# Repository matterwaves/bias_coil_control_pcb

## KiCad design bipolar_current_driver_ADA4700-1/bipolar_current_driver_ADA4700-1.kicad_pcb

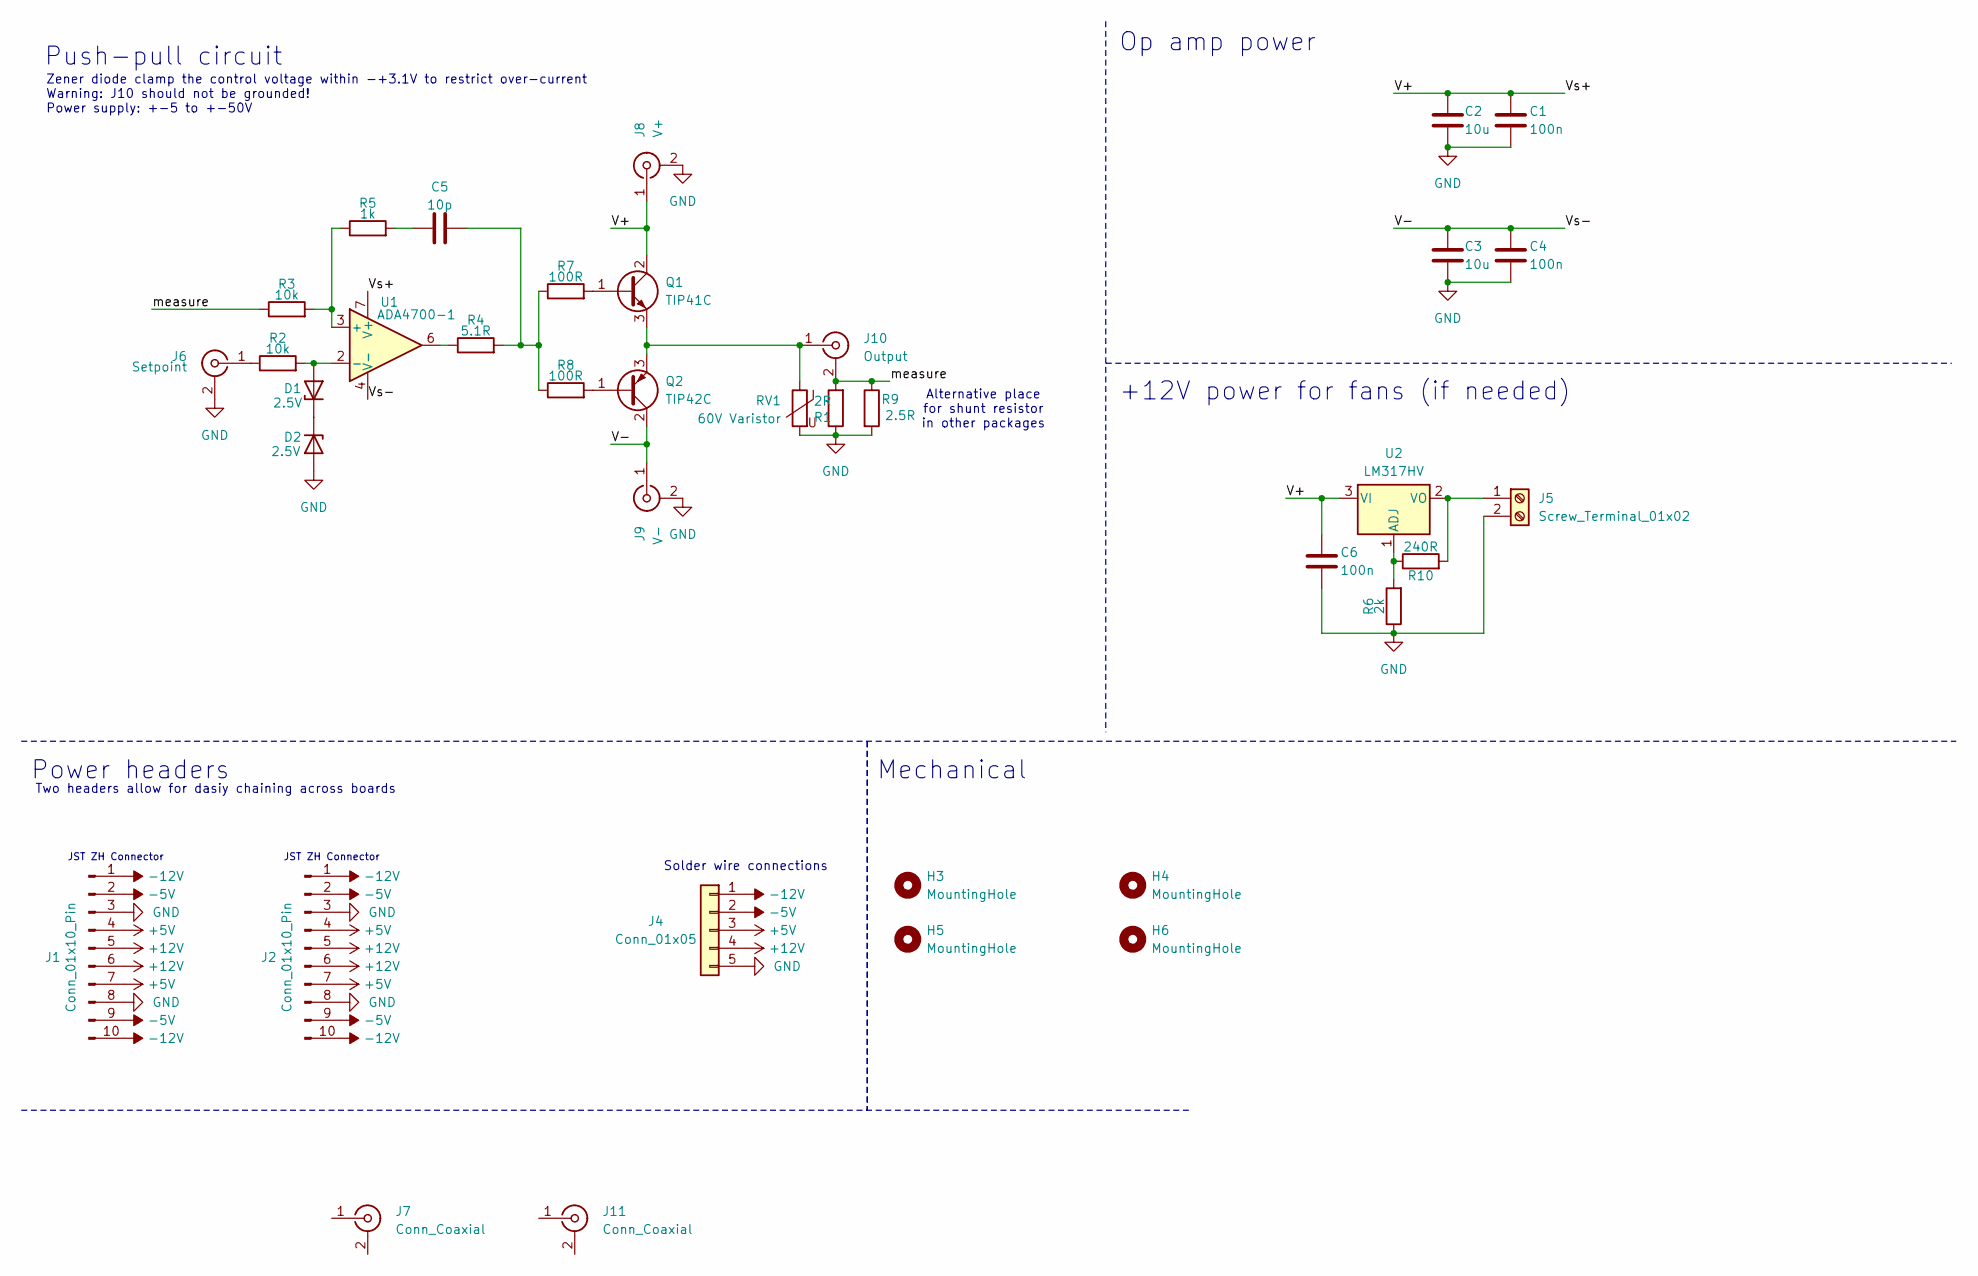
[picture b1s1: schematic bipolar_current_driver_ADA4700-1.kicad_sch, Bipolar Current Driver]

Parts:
C1, C4, C6: 100n; C_1206_3216Metric_Pad1.33x1.80mm_HandSolder; LCSC C1945
C2, C3: 10u; C_Disc_D4.3mm_W1.9mm_P5.00mm; LCSC C2761740
C5: 10p; C_Disc_D5.0mm_W2.5mm_P5.00mm; LCSC C123155
D1, D2: 2.5V; D_DO-35_SOD27_P10.16mm_Horizontal; LCSC C118643
H3, H4, H5, H6: MountingHole; MountingHole_3.2mm_M3
J1, J2: Conn_01x10_Pin; JST_ZH_B10B-ZR_1x10_P1.50mm_Vertical; Digikey PN 455-S10B-ZR-ND
J4: Conn_01x05; SolderWire-0.75sqmm_1x05_P4.8mm_D1.25mm_OD2.3mm
J5: Screw_Terminal_01x02; TerminalBlock_Altech_AK300-2_P5.00mm; Digi-Key Part Number 102-6145-ND
J6: Setpoint; SMA_Molex_73251-1153_EdgeMount_Horizontal; Digikey PN 900-0732511153-ND
J7, J11: Conn_Coaxial; SMA_Molex_73251-1153_EdgeMount_Horizontal; Digikey PN 900-0732511153-ND
J8: V+; SMA_Molex_73251-1153_EdgeMount_Horizontal; Digikey PN 900-0732511153-ND
J9: V-; SMA_Molex_73251-1153_EdgeMount_Horizontal; Digikey PN 900-0732511153-ND
J10: Output; SMA_Molex_73251-1153_EdgeMount_Horizontal; Digikey PN 900-0732511153-ND
Q1: TIP41C; TO-220-3_Horizontal_TabUp; LCSC C92310
Q2: TIP42C; TO-220-3_Horizontal_TabUp; LCSC C92311
R1: 2R; TO-220-2_Horizontal_TabUp; LCSC C19708020
R2, R3: 10k; R_Axial_DIN0207_L6.3mm_D2.5mm_P10.16mm_Horizontal; LCSC C57204
R4: 5.1R; R_Axial_DIN0207_L6.3mm_D2.5mm_P10.16mm_Horizontal; LCSC C58639
R5: 1k; R_Axial_DIN0207_L6.3mm_D2.5mm_P10.16mm_Horizontal; LCSC C57435
R6: 2k; R_1206_3216Metric_Pad1.30x1.75mm_HandSolder; LCSC C17944
R7, R8: 100R; R_Axial_DIN0207_L6.3mm_D2.5mm_P10.16mm_Horizontal; LCSC C57438
R9: 2.5R; R_Axial_Power_L25.0mm_W9.0mm_P30.48mm; LCSC C19708020
R10: 240R; R_1206_3216Metric_Pad1.30x1.75mm_HandSolder; LCSC C17961
RV1: 60V Varistor; RV_Disc_D15.5mm_W6.4mm_P7.5mm
U1: ADA4700-1; SOIC-8_3.9x4.9mm_P1.27mm; LCSC C654219
U2: LM317HV; TO-220-3_Horizontal_TabUp; LCSC C468256

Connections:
+5V: J1.4, J1.7, J2.4, J2.7, J4.3
+12V: J1.5, J1.6, J2.5, J2.6, J4.4
-5V: J1.2, J1.9, J2.2, J2.9, J4.2
-12V: J1.1, J1.10, J2.1, J2.10, J4.1
/V+: C1.1, C2.1, C6.1, J8.1 (In), Q1.2 (C), U1.7 (V+), U2.3 (VI)
/V-: C3.1, C4.1, J9.1 (In), Q2.2 (C), U1.4 (V-)
/measure: J10.2 (Ext), R1.2, R3.1, R9.1
GND: C1.2, C2.2, C3.2, C4.2, C6.2, D2.2 (A), J1.3, J1.8, J2.3, J2.8, J4.5, J5.2, J6.2 (Ext), J8.2 (Ext), J9.2 (Ext), R1.1, R6.1, R9.2, RV1.2
unnamed: C5.1, R5.2
unnamed: C5.2, R4.2, R7.1, R8.1
unnamed: D1.2 (A), R2.2, U1.2 (-)
unnamed: D1.1 (K), D2.1 (K)
unnamed: J5.1, R10.2, U2.2 (VO)
unnamed: J6.1 (In), R2.1
unnamed: J10.1 (In), Q1.3 (E), Q2.3 (E), RV1.1
unnamed: Q1.1 (B), R7.2
unnamed: Q2.1 (B), R8.2
unnamed: R4.1, U1.6
unnamed: R3.2, R5.1, U1.3 (+)
unnamed: R6.2, R10.1, U2.1 (ADJ)

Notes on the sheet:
Solder wire connections
+12V power for fans (if needed)
Mechanical
Alternative place for shunt resistor in other packages
JST ZH Connector
Power headers
Zener diode clamp the control voltage within -+3.1V to restrict over-current Warning: J10 should not be grounded! Power supply: +-5 to +-50V
Two headers allow for dasiy chaining across boards
Op amp power
Push-pull circuit

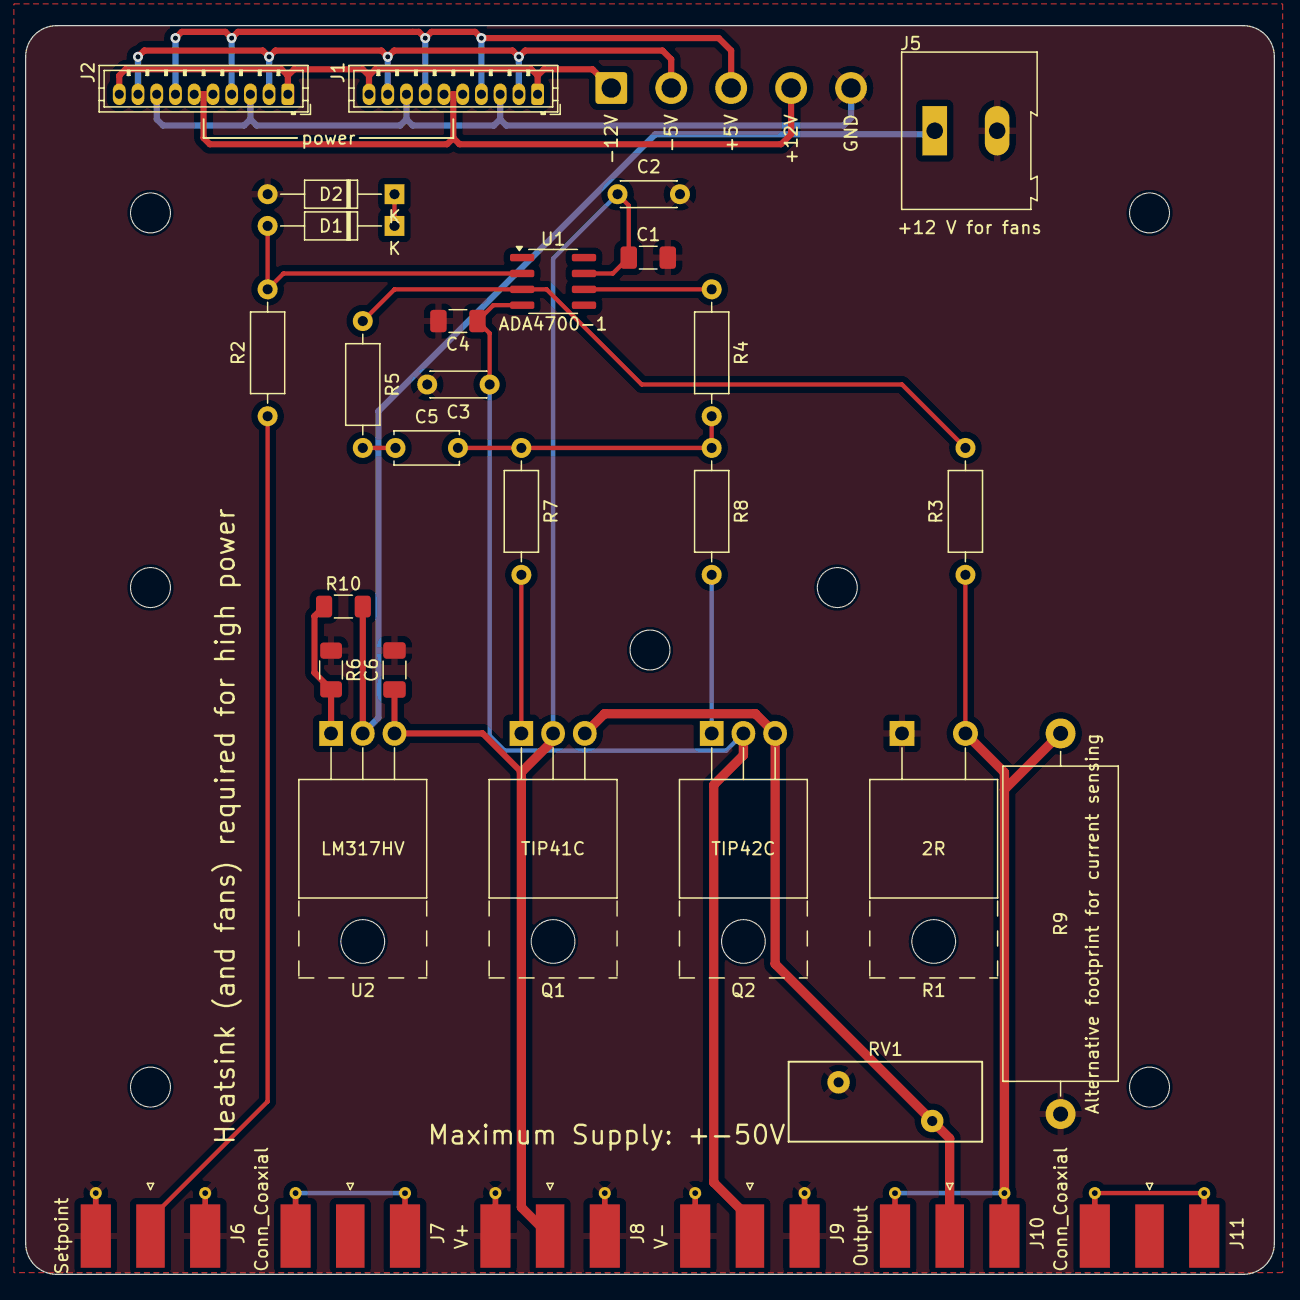
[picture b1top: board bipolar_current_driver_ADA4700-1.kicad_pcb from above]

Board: 4 copper layers, 100.0 x 100.0 mm, 40 parts (0 on the bottom side), 20 nets.

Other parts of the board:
H3#2, H4#2, H4#3: MountingHole; MountingHole_3.2mm_M3

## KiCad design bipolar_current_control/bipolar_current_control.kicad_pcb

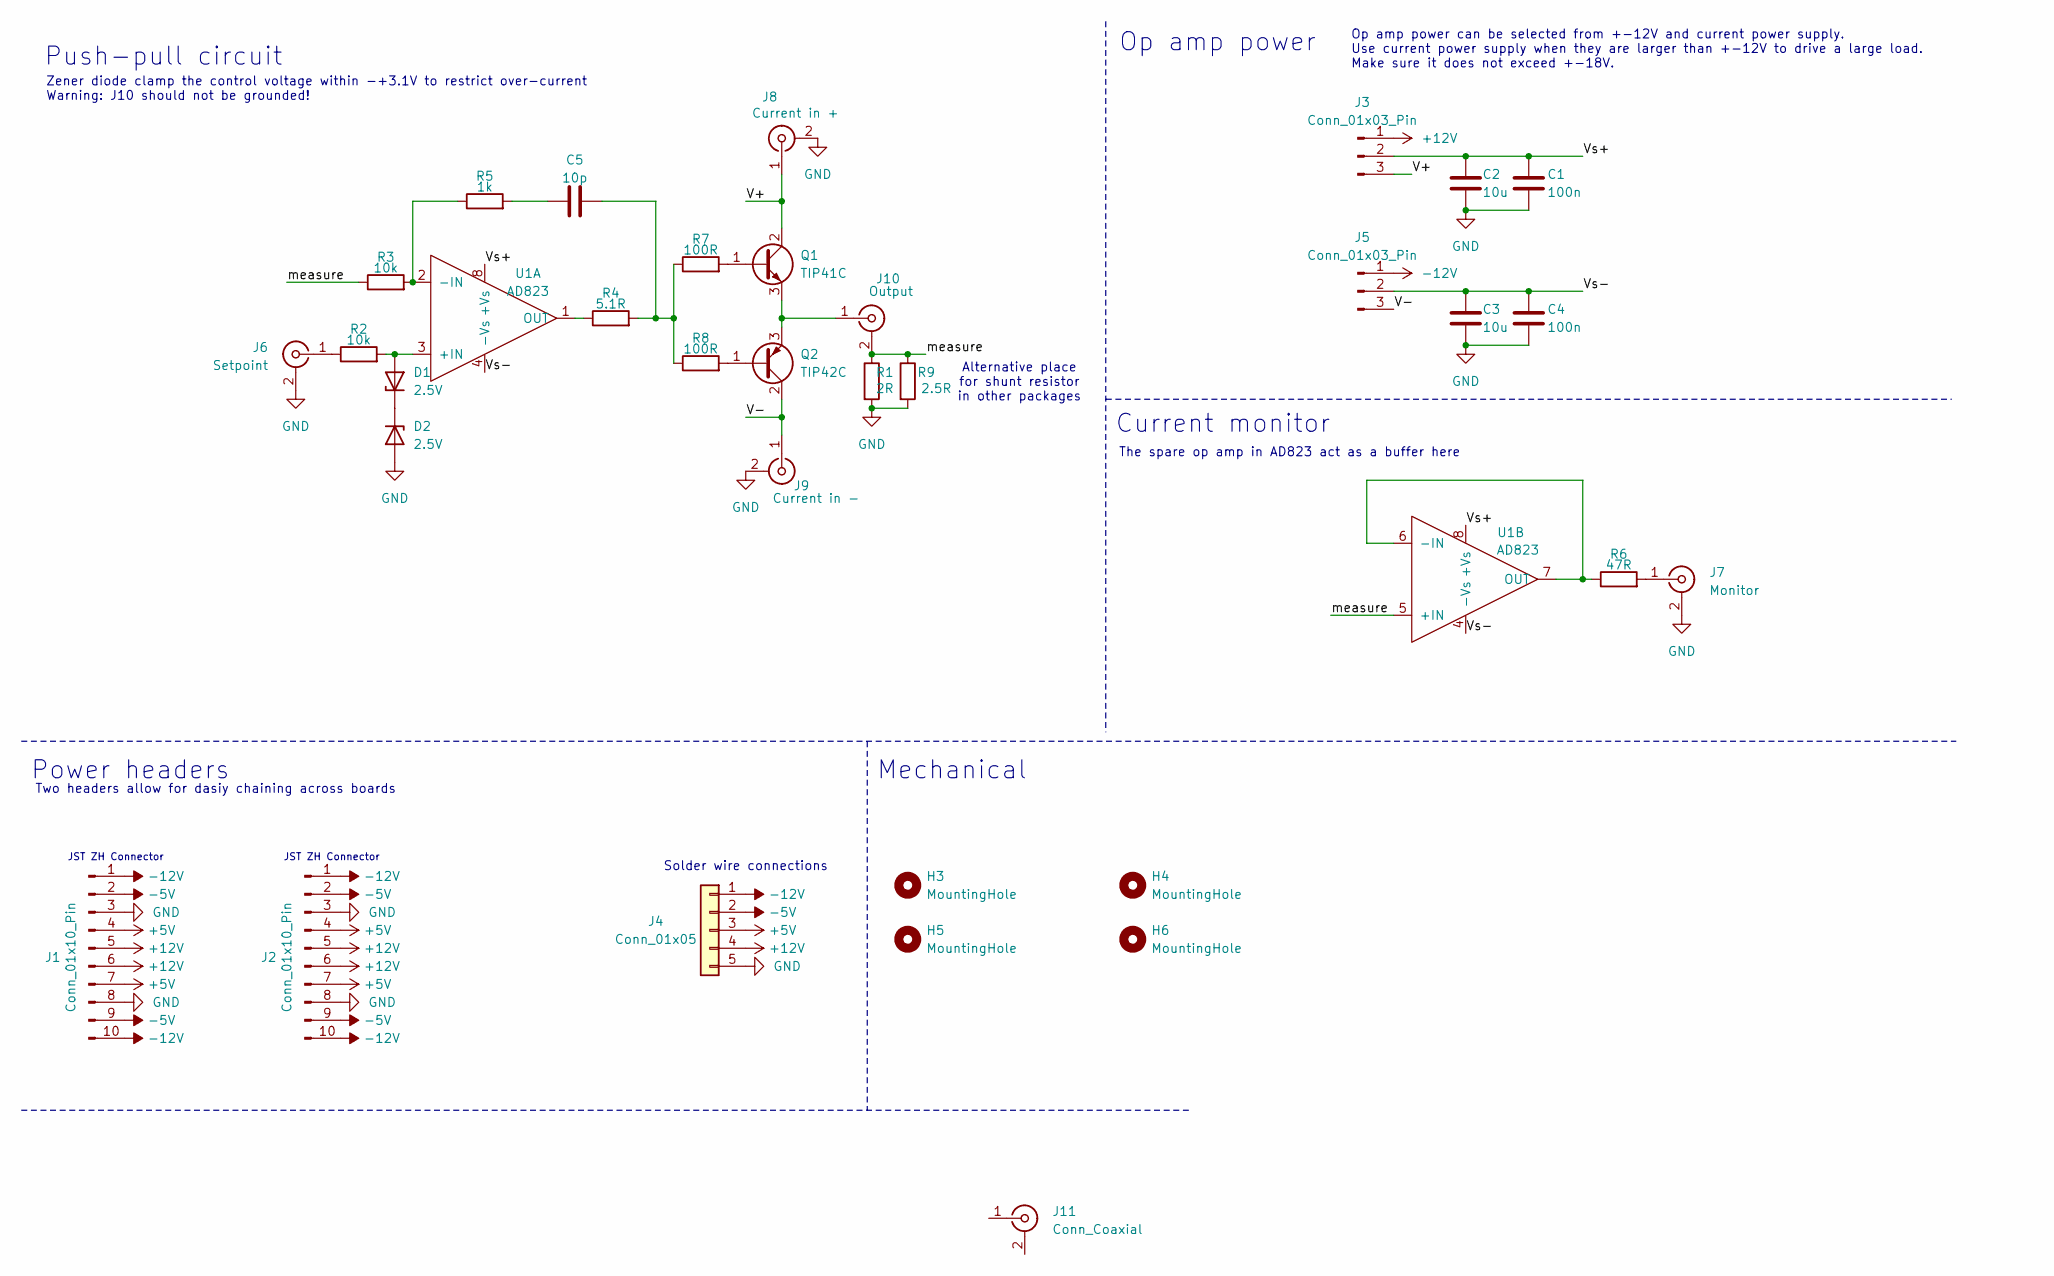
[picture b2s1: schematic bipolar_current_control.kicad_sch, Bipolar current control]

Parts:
C1, C4: 100n; C_Disc_D4.3mm_W1.9mm_P5.00mm; LCSC C84772
C2, C3: 10u; C_Disc_D4.3mm_W1.9mm_P5.00mm; LCSC C2761740
C5: 10p; C_Disc_D5.0mm_W2.5mm_P5.00mm; LCSC C123155
D1, D2: 2.5V; D_DO-35_SOD27_P10.16mm_Horizontal; LCSC C118643
H3, H4, H5, H6: MountingHole; MountingHole_3.2mm_M3
J1, J2: Conn_01x10_Pin; JST_ZH_B10B-ZR_1x10_P1.50mm_Vertical; Digikey PN 455-S10B-ZR-ND
J3, J5: Conn_01x03_Pin; PinHeader_1x03_P2.54mm_Vertical; LCSC C5360899
J4: Conn_01x05; SolderWire-0.75sqmm_1x05_P4.8mm_D1.25mm_OD2.3mm
J6: Setpoint; SMA_Molex_73251-1153_EdgeMount_Horizontal; Digikey PN 900-0732511153-ND
J7: Monitor; SMA_Molex_73251-1153_EdgeMount_Horizontal; Digikey PN 900-0732511153-ND
J8: Current in +; SMA_Molex_73251-1153_EdgeMount_Horizontal; Digikey PN 900-0732511153-ND
J9: Current in -; SMA_Molex_73251-1153_EdgeMount_Horizontal; Digikey PN 900-0732511153-ND
J10: Output; SMA_Molex_73251-1153_EdgeMount_Horizontal; Digikey PN 900-0732511153-ND
J11: Conn_Coaxial; SMA_Molex_73251-1153_EdgeMount_Horizontal; Digikey PN 900-0732511153-ND
Q1: TIP41C; TO-220-3_Vertical; LCSC C92310
Q2: TIP42C; TO-220-3_Vertical; LCSC C92311
R1: 2R; TO-220F-2_Horizontal_TabUp; LCSC C19708020
R2, R3: 10k; R_Axial_DIN0207_L6.3mm_D2.5mm_P10.16mm_Horizontal; LCSC C57204
R4: 5.1R; R_Axial_DIN0207_L6.3mm_D2.5mm_P10.16mm_Horizontal; LCSC C58639
R5: 1k; R_Axial_DIN0207_L6.3mm_D2.5mm_P10.16mm_Horizontal; LCSC C57435
R6: 47R; R_Axial_DIN0207_L6.3mm_D2.5mm_P10.16mm_Horizontal; LCSC C119296
R7, R8: 100R; R_Axial_DIN0207_L6.3mm_D2.5mm_P10.16mm_Horizontal; LCSC C57438
R9: 2.5R; R_Axial_Power_L25.0mm_W9.0mm_P30.48mm; LCSC C19708020
U1: AD823; DIP-8_W7.62mm_Socket_LongPads

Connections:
+5V: J1.4, J1.7, J2.4, J2.7, J4.3
+12V: J1.5, J1.6, J2.5, J2.6, J3.1, J4.4
-5V: J1.2, J1.9, J2.2, J2.9, J4.2
-12V: J1.1, J1.10, J2.1, J2.10, J4.1, J5.1
/V+: J3.3, J8.1 (In), Q1.2 (C)
/V-: J5.3, J9.1 (In), Q2.2 (C)
/Vs+: C1.1, C2.1, J3.2, U1.8 (+Vs)
/Vs-: C3.1, C4.1, J5.2, U1.4 (-Vs)
/measure: J10.2 (Ext), R1.1, R3.1, R9.1, U1.5 (+IN); also elsewhere on the board
GND: C1.2, C2.2, C3.2, C4.2, D2.2 (A), J1.3, J1.8, J2.3, J2.8, J4.5, J6.2 (Ext), J7.2 (Ext), J8.2 (Ext), J9.2 (Ext), R1.2, R9.2; also elsewhere on the board
unnamed: C5.1, R5.2
unnamed: C5.2, R4.2, R7.1, R8.1
unnamed: D1.2 (A), R2.2, U1.3 (+IN)
unnamed: D1.1 (K), D2.1 (K)
unnamed: J6.1 (In), R2.1
unnamed: J7.1 (In), R6.2
unnamed: J10.1 (In), Q1.3 (E), Q2.3 (E)
unnamed: Q1.1 (B), R7.2
unnamed: Q2.1 (B), R8.2
unnamed: R3.2, R5.1, U1.2 (-IN)
unnamed: R4.1, U1.1 (OUT)
unnamed: R6.1, U1.6 (-IN), U1.7 (OUT)

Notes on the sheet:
Solder wire connections
Mechanical
The spare op amp in AD823 act as a buffer here
JST ZH Connector
Power headers
Two headers allow for dasiy chaining across boards
Push-pull circuit
Alternative place for shunt resistor in other packages
Op amp power can be selected from +-12V and current power supply. Use current power supply when they are larger than +-12V to drive a large load. Make sure it does not exceed +-18V.
Current monitor
Zener diode clamp the control voltage within -+3.1V to restrict over-current Warning: J10 should not be grounded!
Op amp power

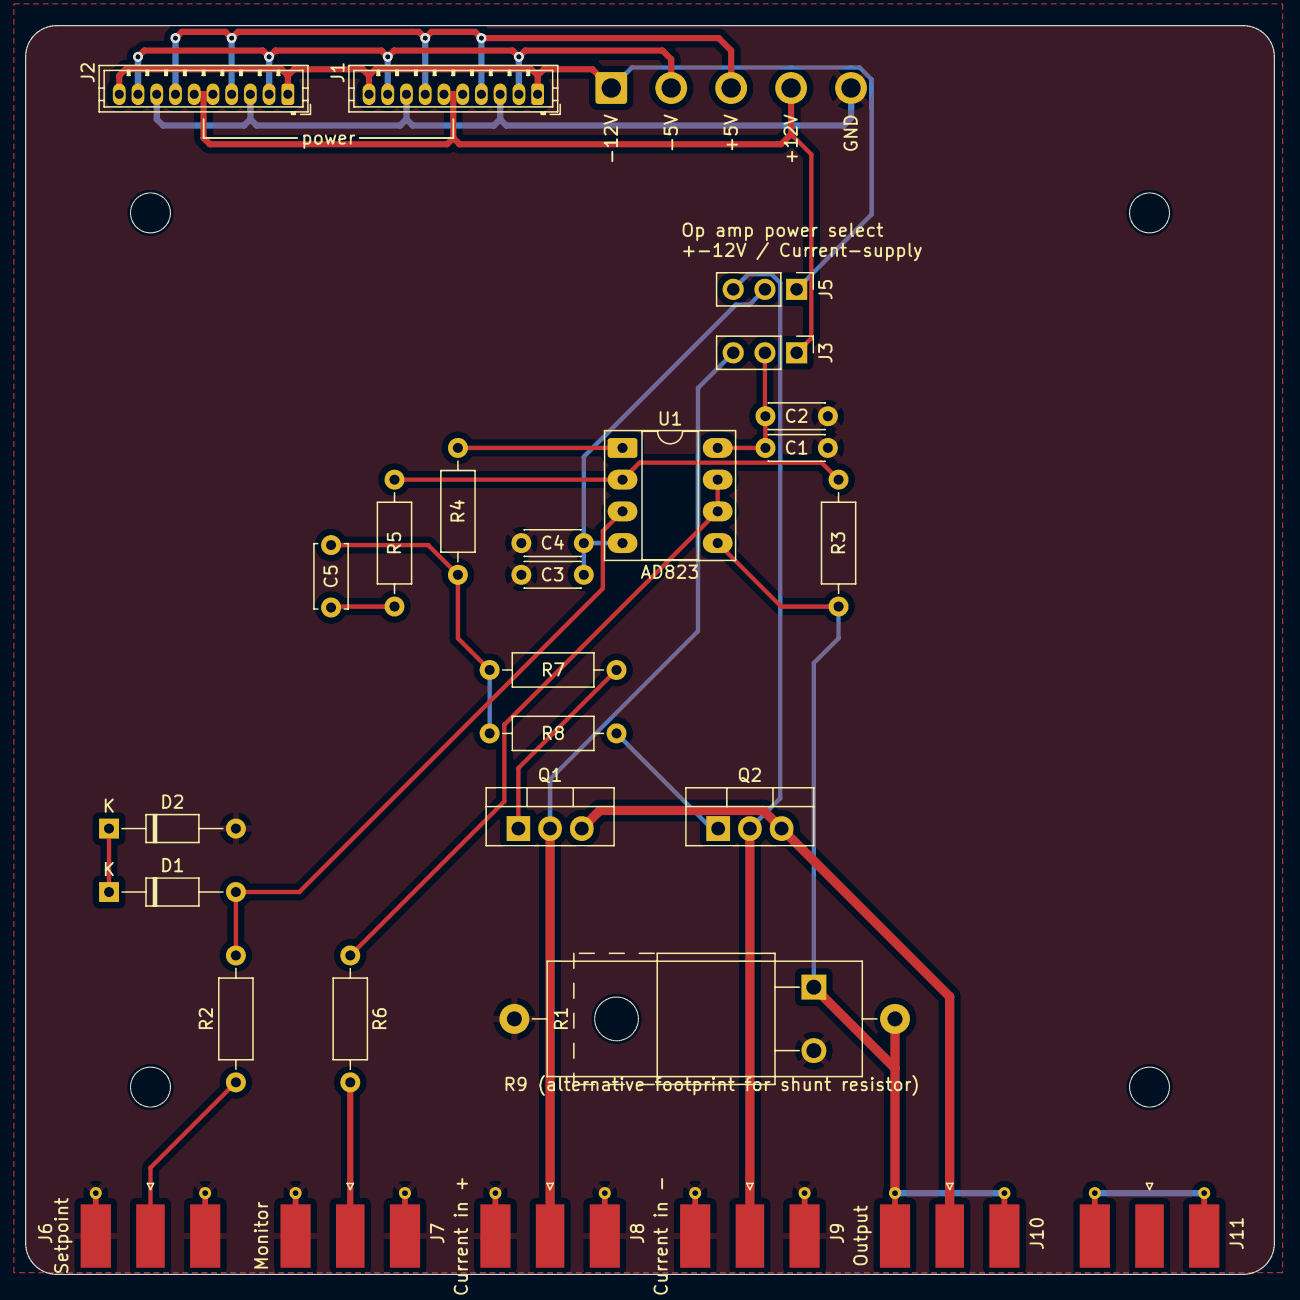
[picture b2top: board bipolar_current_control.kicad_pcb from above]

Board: 4 copper layers, 100.0 x 100.0 mm, 34 parts (0 on the bottom side), 22 nets.

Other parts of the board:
R9 (alternative footprint for shunt resistor): 2.5R; R_Axial_Power_L25.0mm_W9.0mm_P30.48mm

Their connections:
/measure: R9 (alternative footprint for shunt res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.1; also elsewhere on the board
GND: R9 (alternative footprint for shunt res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.2; also elsewhere on the board

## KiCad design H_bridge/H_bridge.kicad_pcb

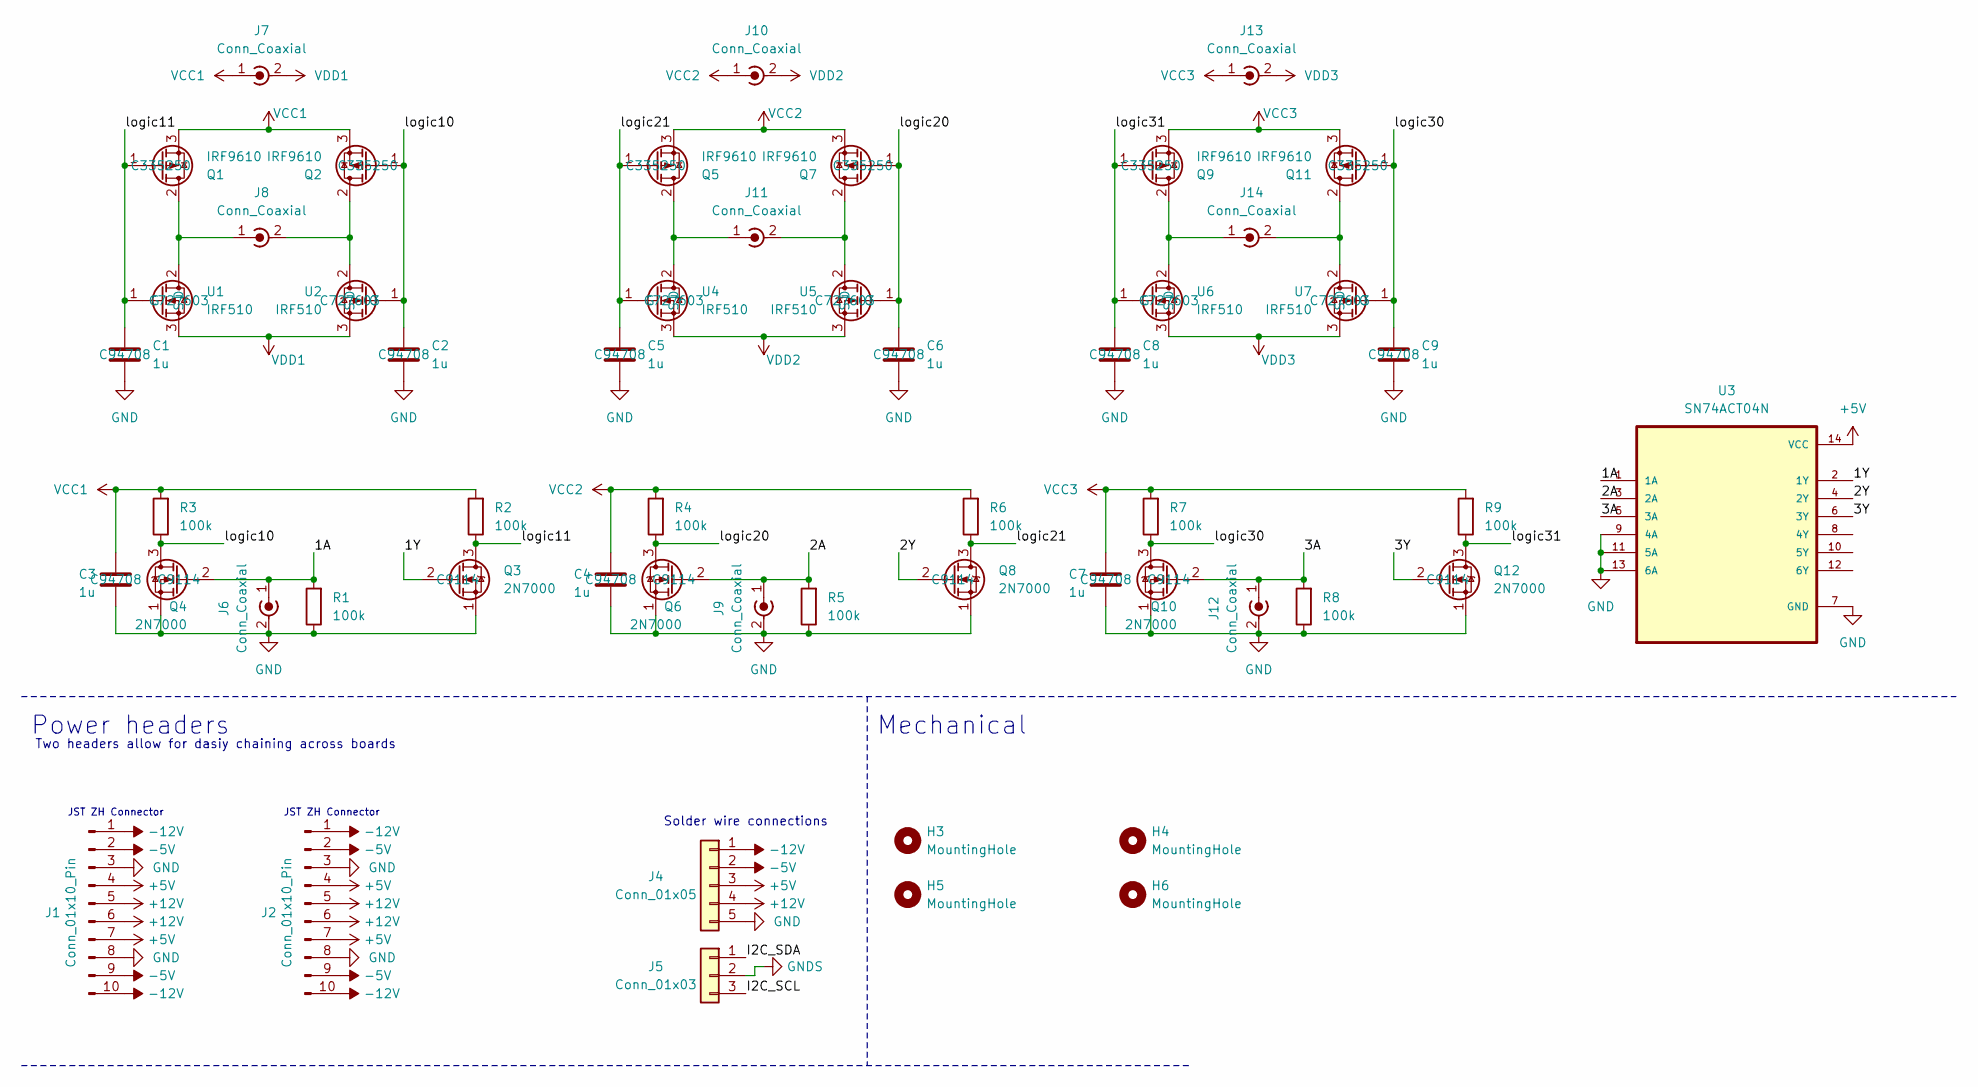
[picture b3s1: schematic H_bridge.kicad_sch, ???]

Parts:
C1, C2, C3, C4, C5, C6, C7, C8, C9: 1u; C_Disc_D4.3mm_W1.9mm_P5.00mm; LCSC C94708
H3, H4, H5, H6: MountingHole; MountingHole_3.2mm_M3
J1, J2: Conn_01x10_Pin; JST_ZH_B10B-ZR_1x10_P1.50mm_Vertical; Digikey PN 455-S10B-ZR-ND
J4: Conn_01x05; SolderWire-0.75sqmm_1x05_P4.8mm_D1.25mm_OD2.3mm
J5: Conn_01x03; SolderWire-0.75sqmm_1x03_P4.8mm_D1.25mm_OD2.3mm
J6, J7, J8, J9, J10, J11, J12, J13, J14: Conn_Coaxial; SMA_Molex_73251-1153_EdgeMount_Horizontal
Q1, Q2, Q5, Q7, Q9, Q11: IRF9610; TO-220-3_Vertical; LCSC C335250
Q3, Q4, Q6, Q8, Q10, Q12: 2N7000; TO-92_Inline; LCSC C9114
R1, R2, R3, R4, R5, R6, R7, R8, R9: 100k; R_Axial_DIN0207_L6.3mm_D2.5mm_P10.16mm_Horizontal
U1, U2, U4, U5, U6, U7: IRF510; TO-220-3_Vertical; Digi-Key Part Number IRF520PBF-ND
U3: SN74ACT04N; DIP-14_W7.62mm_Socket_LongPads

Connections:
+5V: J1.4, J1.7, J2.4, J2.7, J4.3, U3.14 (VCC)
+12V: J1.5, J1.6, J2.5, J2.6, J4.4
-5V: J1.2, J1.9, J2.2, J2.9, J4.2
-12V: J1.1, J1.10, J2.1, J2.10, J4.1
/1A: J6.1 (In), Q4.2 (G), R1.2, U3.1 (1A)
/1Y: Q3.2 (G), U3.2 (1Y)
/2A: J9.1 (In), Q6.2 (G), R5.2, U3.3 (2A)
/2Y: Q8.2 (G), U3.4 (2Y)
/3A: J12.1 (In), Q10.2 (G), R8.2, U3.5 (3A)
/3Y: Q12.2 (G), U3.6 (3Y)
/I2C_SCL: J5.3
/I2C_SDA: J5.1
/logic10: C2.1, Q2.1 (G), Q4.3 (D), R3.1, U2.1 (G)
/logic11: C1.1, Q1.1 (G), Q3.3 (D), R2.1, U1.1 (G)
/logic20: C6.1, Q6.3 (D), Q7.1 (G), R4.1, U5.1 (G)
/logic21: C5.1, Q5.1 (G), Q8.3 (D), R6.1, U4.1 (G)
/logic30: C9.1, Q10.3 (D), Q11.1 (G), R7.1, U7.1 (G)
/logic31: C8.1, Q9.1 (G), Q12.3 (D), R9.1, U6.1 (G)
GND: C1.2, C2.2, C3.2, C4.2, C5.2, C6.2, C7.2, C8.2, C9.2, J1.3, J1.8, J2.3, J2.8, J4.5, J6.2 (Ext), J9.2 (Ext), J12.2 (Ext), Q3.1 (S), Q4.1 (S), Q6.1 (S), Q8.1 (S), Q10.1 (S), Q12.1 (S), R1.1, R5.1, R8.1, U3.7 (GND), U3.9 (4A), U3.11 (5A), U3.13 (6A)
GNDS: J5.2
unnamed: J8.2 (Ext), Q2.2 (D), U2.2 (D)
unnamed: J8.1 (In), Q1.2 (D), U1.2 (D)
unnamed: J11.2 (Ext), Q7.2 (D), U5.2 (D)
unnamed: J11.1 (In), Q5.2 (D), U4.2 (D)
unnamed: J14.2 (Ext), Q11.2 (D), U7.2 (D)
unnamed: J14.1 (In), Q9.2 (D), U6.2 (D)
VCC1: C3.1, J7.1 (In), Q1.3 (S), Q2.3 (S), R2.2, R3.2
VCC2: C4.1, J10.1 (In), Q5.3 (S), Q7.3 (S), R4.2, R6.2
VCC3: C7.1, J13.1 (In), Q9.3 (S), Q11.3 (S), R7.2, R9.2
VDD1: J7.2 (Ext), U1.3 (S), U2.3 (S)
VDD2: J10.2 (Ext), U4.3 (S), U5.3 (S)
VDD3: J13.2 (Ext), U6.3 (S), U7.3 (S)

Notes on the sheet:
Solder wire connections
Mechanical
JST ZH Connector
Power headers
Two headers allow for dasiy chaining across boards

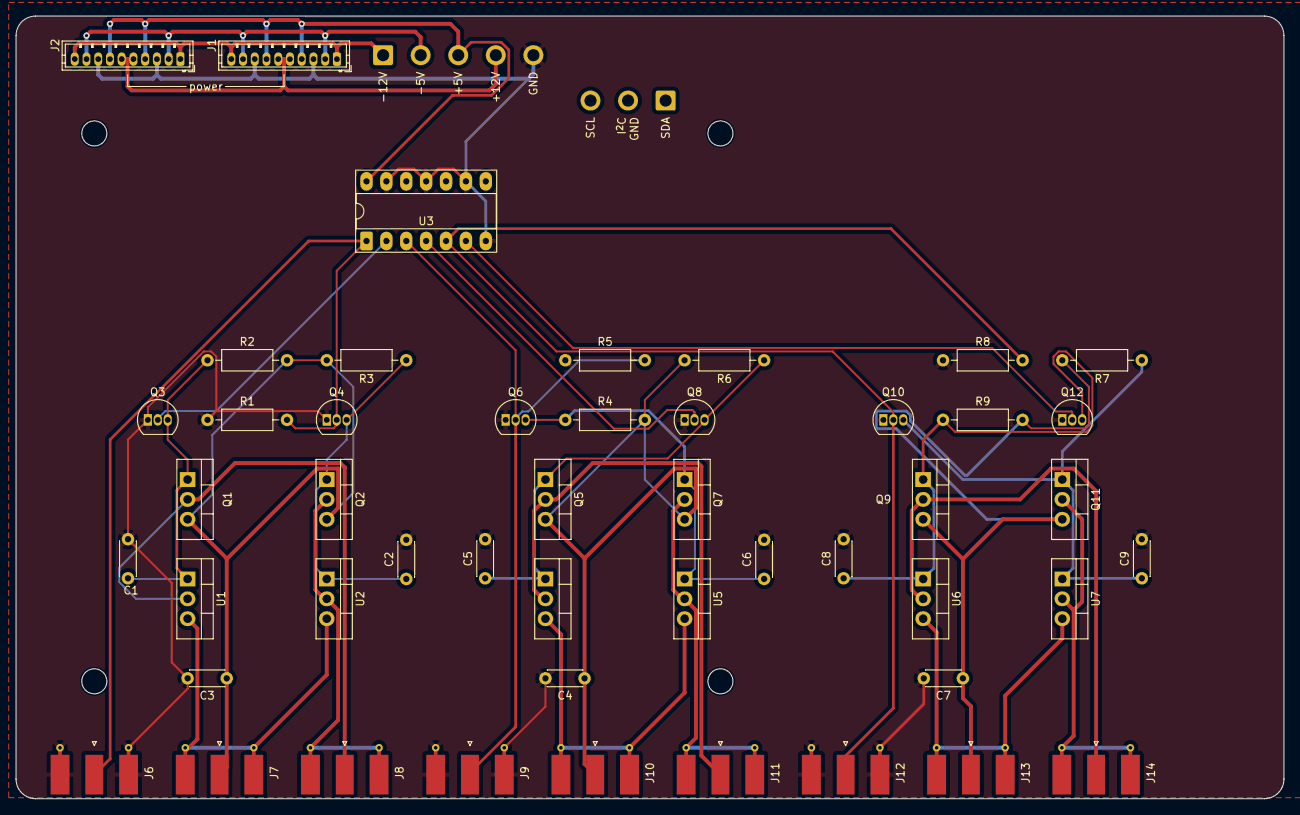
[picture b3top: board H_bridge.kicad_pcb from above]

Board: 4 copper layers, 162.0 x 100.0 mm, 54 parts (0 on the bottom side), 29 nets.

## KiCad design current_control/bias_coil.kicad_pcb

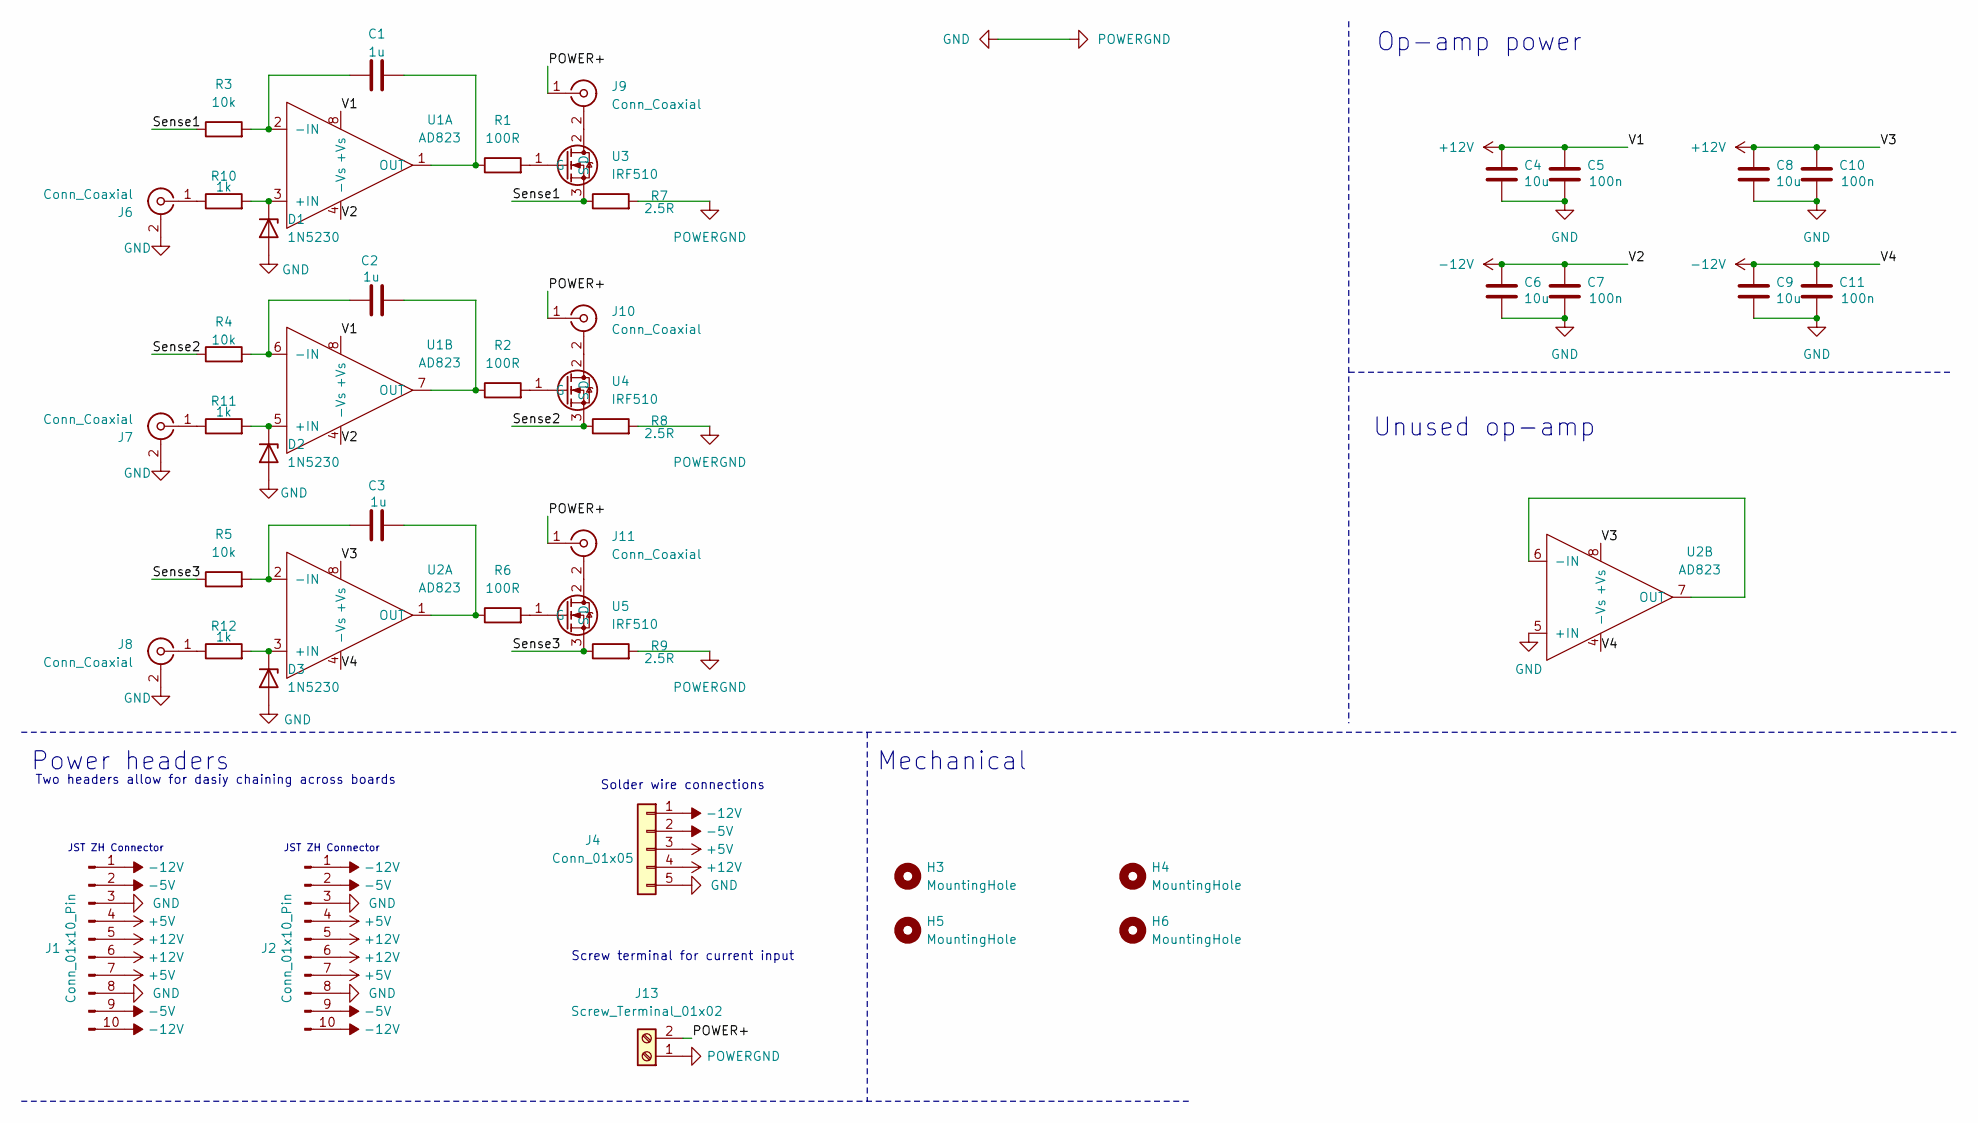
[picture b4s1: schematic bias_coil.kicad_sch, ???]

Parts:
C1, C2, C3: 1u; C_Disc_D4.3mm_W1.9mm_P5.00mm
C4, C6, C8, C9: 10u; C_Disc_D4.3mm_W1.9mm_P5.00mm
C5, C7, C10, C11: 100n; C_Disc_D4.3mm_W1.9mm_P5.00mm
D1, D2, D3: 1N5230; D_A-405_P10.16mm_Horizontal
H3, H4, H5, H6: MountingHole; MountingHole_3.2mm_M3
J1, J2: Conn_01x10_Pin; JST_ZH_B10B-ZR_1x10_P1.50mm_Vertical; Digikey PN 455-S10B-ZR-ND
J4: Conn_01x05; SolderWire-0.75sqmm_1x05_P4.8mm_D1.25mm_OD2.3mm
J6, J7, J8, J9, J10, J11: Conn_Coaxial; SMA_Molex_73251-1153_EdgeMount_Horizontal; Digikey PN 900-0732511153-ND
J13: Screw_Terminal_01x02; TerminalBlock_bornier-2_P5.08mm
R1, R2, R6: 100R; R_Axial_DIN0207_L6.3mm_D2.5mm_P10.16mm_Horizontal
R3, R4, R5: 10k; R_Axial_DIN0207_L6.3mm_D2.5mm_P10.16mm_Horizontal
R7, R8, R9: 2.5R; R_Axial_Power_L25.0mm_W6.4mm_P30.48mm
R10, R11, R12: 1k; R_Axial_DIN0207_L6.3mm_D2.5mm_P10.16mm_Horizontal
U1, U2: AD823; DIP-8_W7.62mm_Socket_LongPads
U3, U4, U5: IRF510; TO-220-3_Vertical; Digi-Key Part Number IRF520PBF-ND

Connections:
+5V: J1.4, J1.7, J2.4, J2.7, J4.3
+12V: C4.2, C5.2, C8.2, C10.2, J1.5, J1.6, J2.5, J2.6, J4.4, U1.8 (+Vs), U2.8 (+Vs)
-5V: J1.2, J1.9, J2.2, J2.9, J4.2
-12V: C6.2, C7.2, C9.2, C11.2, J1.1, J1.10, J2.1, J2.10, J4.1, U1.4 (-Vs), U2.4 (-Vs)
/POWER+: J9.1 (In), J10.1 (In), J11.1 (In), J13.2
/Sense1: R3.1, R7.1, U3.3 (S)
/Sense2: R4.1, R8.1, U4.3 (S)
/Sense3: R5.1, R9.1, U5.3 (S)
GND: C4.1, C5.1, C6.1, C7.1, C8.1, C9.1, C10.1, C11.1, D1.2 (A), D2.2 (A), D3.2 (A), J1.3, J1.8, J2.3, J2.8, J4.5, J6.2 (Ext), J7.2 (Ext), J8.2 (Ext), J13.1, R7.2, R8.2, R9.2, U2.5 (+IN)
unnamed: D1.1 (K), R10.2, U1.3 (+IN)
unnamed: D2.1 (K), R11.2, U1.5 (+IN)
unnamed: D3.1 (K), R12.2, U2.3 (+IN)
unnamed: J6.1 (In), R10.1
unnamed: J7.1 (In), R11.1
unnamed: J8.1 (In), R12.1
unnamed: J9.2 (Ext), U3.2 (D)
unnamed: J10.2 (Ext), U4.2 (D)
unnamed: J11.2 (Ext), U5.2 (D)
unnamed: C1.1, R3.2, U1.2 (-IN)
unnamed: C1.2, R1.1, U1.1 (OUT)
unnamed: C2.1, R4.2, U1.6 (-IN)
unnamed: C2.2, R2.1, U1.7 (OUT)
unnamed: C3.1, R5.2, U2.2 (-IN)
unnamed: C3.2, R6.1, U2.1 (OUT)
unnamed: U2.6 (-IN), U2.7 (OUT)
unnamed: R1.2, U3.1 (G)
unnamed: R2.2, U4.1 (G)
unnamed: R6.2, U5.1 (G)

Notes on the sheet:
Solder wire connections
Screw terminal for current input
Unused op-amp
Mechanical
Op-amp power
JST ZH Connector
Power headers
Two headers allow for dasiy chaining across boards

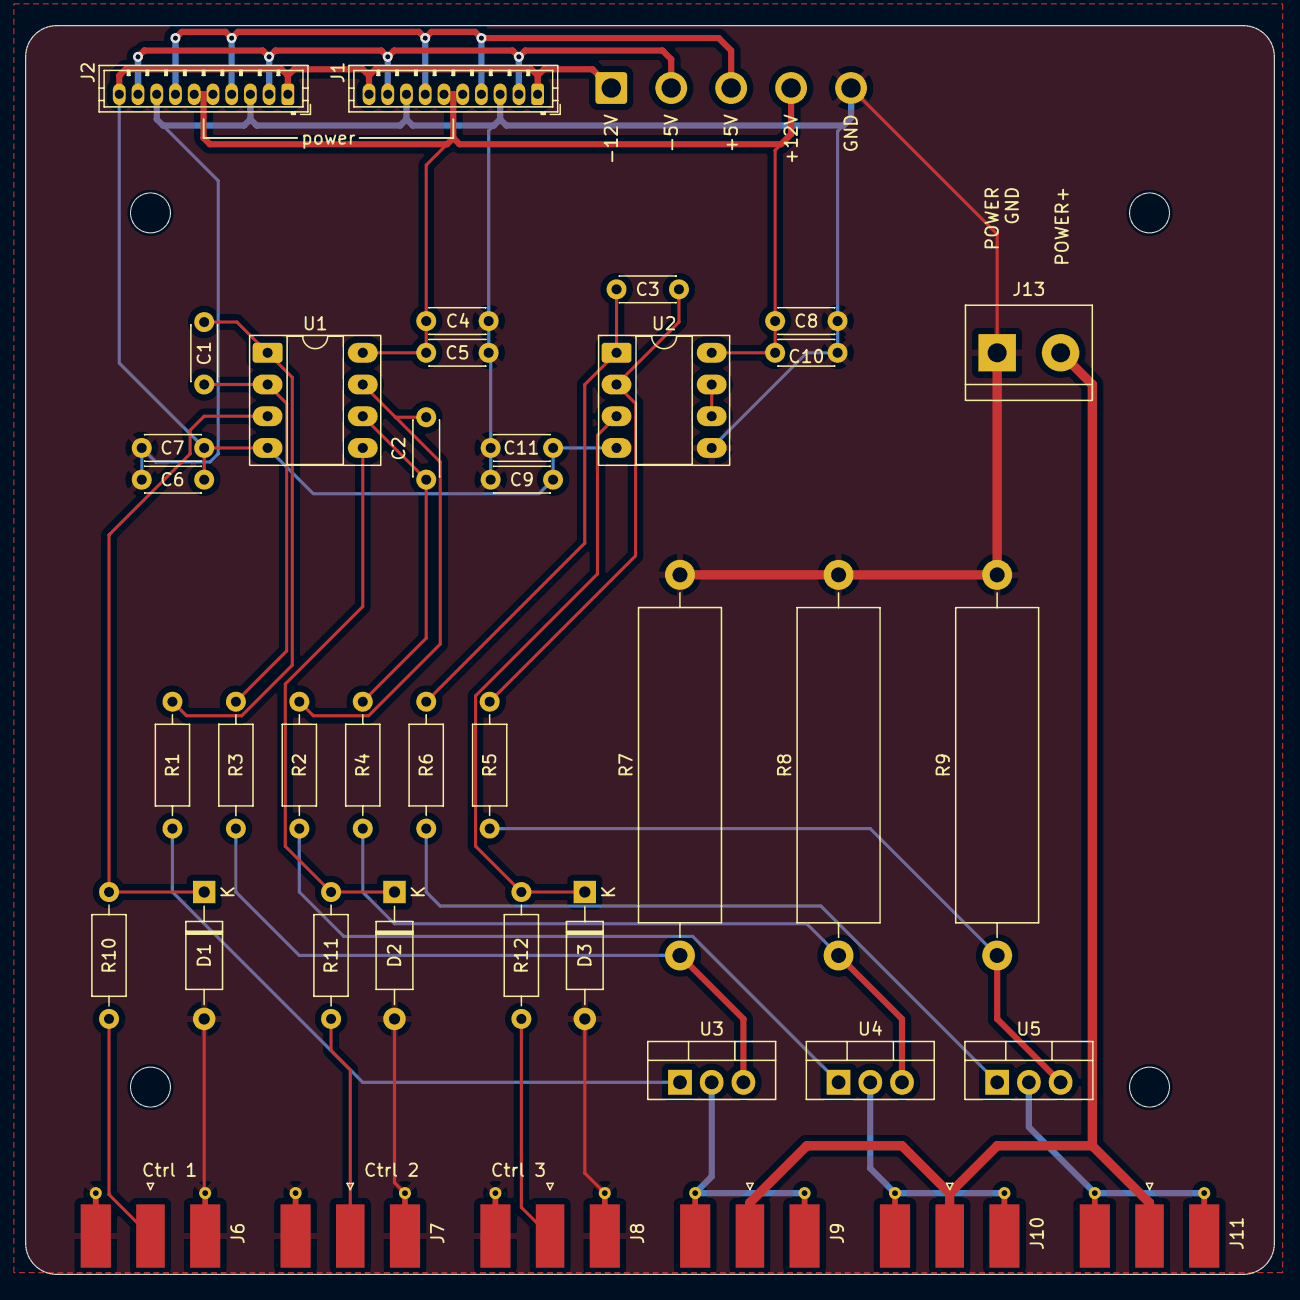
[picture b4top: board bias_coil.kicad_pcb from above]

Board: 4 copper layers, 100.0 x 100.0 mm, 45 parts (0 on the bottom side), 28 nets.

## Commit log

2025-06-03 Initial
2025-06-03 create H-bridge circuit folder
2025-06-03 add production files for current control pcb
2025-06-04 updated 3-channel H-bridge
2025-06-04 generate production files for H-bridge
2025-06-05 create bipolar current driver
2025-06-05 add a grounded version of bipolar current driver
2025-06-05 add a grounded-output for bipolar current source
2025-06-06 layout PCB for grounded bipolar
2025-07-04 update circuit with op amp power selection
2025-07-04 add production files
2025-07-08 add design with ADA4700-1
